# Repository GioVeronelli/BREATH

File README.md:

<h1 align="center"> B(R)EAT(H) </h1>

## Getting Started
### Clone the repository
Run the command on your terminal at the desired location:
```
git clone git@github.com:ltebs-polimi/AY2324_II_Project-1.git
```
### Dependencies
It is recommended to create a virtual environment to run the GUI. This can be done by running on your terminal:
```
python -m virtualenv GUI_venv
```
The latest versions of these libraries should then be installed within the virtual environment:
- ```PyQt5```
- ```numpy```
- ```scipy```
- ```pandas```
- ```openpyxl```
- ```pyqtgraph```
- ```os```
- ```sys```
- ```time```
- ```logging```
- ```struct```
- ```subprocess```
- ```sqlite3```
- ```csv```
- ```datetime```
- ```serial```
## Filetree
Directories are organized as follows:
```
││├───CASE
│││   └──STL files
│││
││├───GUI
│││   ├──pyqt5_venv
│││   └──GUI.py
│││
││├───PCB
│││   ├──B(R)EAT(H).bdr
│││   └──B(R)EAT(H).sch
│││
││└───PSoC_code
││    ├──GatheringData.cydsn
││       │
││       ├───Generated_Source
││       │   └───PSoC5
││       └───TopDesign
││
│└───Validation_Study
│    ├──Output_Measurements
│    └──Plots
│
└───Images

```

## Intro
There are several methods for assessing general respiratory health. The most common methods are pulmonary function tests (PFTs) that range from simple spirometry, which can be used to assess a patient’s airflow, to full body plethysmography used to assess lung volumes. Other methods include arterial blood sampling and diffusion capacity. While these evaluations are effective in assessing a patient’s respiratory health at a specific point in time in a laboratory setting, they cannot continuously monitor a patient’s respiratory state under normal daily environments. Moreover, PFTs such as spirometry require the patient to breathe maximally into a mouthpiece, a maneuver that is challenging, which makes these types of tests difficult to ensure accurate readings and are not suitable for long term use.[^1] Other methods for sensing the respiratory signal include measuring airflow through the nostrils with a pressure transducer in combination with a spirometer, and tracking chest wall movement with a piezoelectric belt.[^2] These techniques are essential for monitoring breathing of patients with respiartory disorders,chronic obstructive pulmonary disease, or neuromuscolar disorders, as they allow for the assessment of the stability of their conditions. 
An emergin area of interest is the use of motion sensors, such as accelerometers fixed on the chest or abdomen, as a comfortable, and cheap method for respiratory monitoring. The main aim of the study group is to evaluate the feasibility of implementing an accelerometry-based portable device as a simple and cost-effective solution for monitoring breathing patterns and parameters.
Respiratory disorders significantly impair lung capacity and respiratory function thus the need of developing an accurate monitoring to prevent sever conmplication and to adjust therapies promptly. Traditional monitoring techniques, although effective, can be cumbersome and uncomfrtable for partients, restricting their mobility. Therefore, developing portable devices based on accelerometers could revolutionize the clincial management of these patients by providing precise data onc hest and abdominal movements associated with breathing, enabling continuous and non-invasive monitoring. This approach could enhance the quality of life for patients by allowing them to perform daily axctivities with fewer restrictions while ensuring accurate monitoring of their clinical condition.

However,beside the developed technical features, the ethics behind measuring the subject's respiratory parameters should also be considered. The primary goal of clinical research is to develop generalizable knowledge that improves human health or increases understanding of human biology. People who participate in clinical research make it possible to secure that knowledge ensuring at the same time that subjects involved do not suffer violations of their rights, as clinical trials can expose them to significant risks. The purpose of ethical guidelines is both to protect patient volunteers and to preserve the integrity of science.[^3]

The details of the project are discussed in the following sections:
- [Hardware](#hardware)
- [Firmware](#firmware)
- [Processing](#processing)
- [Graphical user interface](#graphical-user-interface)
- [Acquisition Protocol](#acquisition-protocol)  
- [Limitations and future developments](#limitations-and-future-developments)

   <br> 

## Hardware
### Reference Folder: `PCB`, `Case_3Dprint`
  
B(R)EAT(H) is a wereable device mainly composed by LIS3DH accelerometer hold to a 3D printed support case and then fixed position on the abdomen of the subject via an elastic band.  

<br> 

<div align="center">

</div>

<br>

The electronic circuit has been simulated in breaboard before designing the PCB.   
The electronical components used for the main module are: 
- Psoc 5LP, accelerometer LIS3DH, bluetooth module HC-O5, 9V alkaline battery, switch, linear voltage regulator LM7805, resistors (330Ω 3x), capacitors (0.1 μF 1x, 0.33μF 1x)
<br>

### 3D Printed Case design discussion:
- The 3D printed case is meant to contain the PCB with all the peripherals except for the accelerometer, which is instead fixed through screws and worn on the front of the subject depending on the user selected protocol and fixed in position by an elastic band. They were both built using Tinkercad app.

Below you can see the case for holding the accelerometer:

<br> 

<div align="center">

</div>

<br>

While here it is represented the 3d printed case design:

<br> 

<div align="center">

</div>

<br>

### Hardware functioning discussion:
- The accelerometer LIS3DH communicates with the microcontroller via I2C master-slave communication, whereas the bluetooth module communicates via UART communication.
- The accelerometer has also a connection between its interrupt pin and 2.2 pin of the microcontroller, so that it can trigger an interrupt when data are available. 
- The PSOC 5LP and all the peripherals run on 5V, so the 9V of the battery is reduced and stabilized to 5V by the linear voltage regulator LM7805 and capacitors. 
- Resistors are used to limit the current running in the RGB led and to reduce the TX signal sent by the microcontroller to the bluetooth module from 5V to 3.3V, to cope with the HC-05 input pin limitations. 
- The active buzzer is used to advice the operator that the patient is breathing in a non phisiological way.
- The RBG LED is meant to signal the connection status of the device. Initially, while the device is not yet paired with the laptop, the LED will blink in RED driven by a PWM signal with a period of 1 second and duty cycle of 50%. Successful pairing is then flagged via a fixed blue light, while during data streaming a fixed green light is shown.

From a hardware perspective, we have considered three distinct methods for interaction between the subject and the device. 
First, the subject can control the device's power using an external switch to turn it on or off. 
Second, an RGB LED provides communication with the caregiver by indicating the device’s functional status. 
Finally, the buzzer serves as an additional alert mechanism, sounding an alarm if physiological measurements exceed predefined thresholds. This setup ensures that caregivers receive immediate notifications not only through the app screen but also via a distinct auditory signal.

Here it is possible to appreciate the whole device mounted on the designed PCB obtained through the press and peel technique:

<br> 

<div align="center">

</div>

<br>

## Firmware
### Reference Folder: `PSoC_CODE`
In this section it is reported the description of the code written using PSoC Creator, regarding the firmware functionalities of the PSoC5LP for commanding B(R)EAT(H) device. In the "main.c" file we have the main recommended settings for RR measurement such as: 
- 12bit resolution with high power configuration. 
- +2/-2g full scale.
- 200Hz as ODR (Output Data Rate).

Regarding "InterruptRoutines.c", the ISR function "CY_ISR(Custom_ISR_Data)" is called whenever a new value of acceleration on the Z-axis is available. This triggers the call of the script where the data is reconstructed into its binary representation and sent to the UART TX, corresponding to the RX of the HC05 for Bluetooth communication. The data stream is triggered whenever the caregiver starts the connection with the device from the GUI, which corresponds on writing a letter "s" to the TX of the HC05, associated with the RX of the UART of the PSoC through the ISR function "CY_ISR(Custom_ISR_RX)". Indeed, this function manages signals written to the TX pin of the HC05 for setting the BUZZER,LED_R,LED_B,LED_G and PWM components depending on the device operating status. This ensures that the app user can communicate with the device both from the PSoC to the GUI through the HC05, and then back from the GUI to the PSoC. This allows to have a better interaction and dinamism in the use of the app.
The ISR function "CY_ISR(Custom_ISR_RX)" is commands the RGB led and BUZZER based on the character received from the GUI which is linked to the functioning status of the device. When turned on, the PWM on LED_R blinks with a frequency of 1 second and a duty cycle of 50%. Successful pairing is then flagged via a fixed blue light, while a fixed green light is shown during data streaming. If the RR parameter is out of physiological range, depending on the selected acquistion protocol, the active BUZZER is activated to alert the caregivers drawing attention to the subject's breathing and activity that triggered the BUZZER. 

## Processing
### Reference Folder: `GUI`

For the device, two distinct data processing procedures were developed: one for real-time data processing and the other for offline data processing.

#### Real-Time Data Processing

Multiple processing techniques were developed and tested. The chosen method, despite its apparent simplicity, proved to be the most effective considering both the quality of filtering and the adaptation time. The final steps for real-time processing are as follows:
- The acquired data from the serial worker is added to a buffer ('data_buffer') that stores all the measured acceleration values coming from the accelerometer.
- A moving average filter is applied to the buffered data to smooth rapid fluctuations and stabilize the signal. The chosen window size is 200 points, corresponding to 1 second of acquisition. If the buffer contains fewer than 200 data points, the filter will wait until the chosen window size is reached to start.
- Then, a third order low-pass Butterworth filter is applied to the moving average filtered data, with a chosen cutoff frequency of 0.6 Hz. The buffer size must contain at least 12 data points before applying the filter; otherwise, the filter waits until this limit is reached.
- After this processing, the peaks and lows are identified in the signal using the find_peaks algorithm from the SciPy library. This step identifies both the points of maximum, which indicate the end of an inspiration and the beginning of an expiration, and the points of minimum, which indicate the opposite in the acceleration signal. To distinguish between real and local minima and maxima, a prominence level is chosen. Specifically, when the subject is standing, the chosen prominence is 0.15, while when sitting, it is 0.05.
- To better compute the parameters and allow the filters time to adapt, the first fiducial point identified is always a minimum. If a maximum is identified before the first minimum, it is discarded. This ensures that the filtered signal always begins with the start of a respiratory cycle.
- After these computations, the parameters are computed. The chosen parameters are: the instantenous respiratory rate, the inspiratory time, the expiratory time and the inspiratory/expiratory ratio. Each of these parameters is updated every new cycle detected.
- Starting from the instantaneous RR, it is calculated as the difference between the time index of two subsequent minima. At least two lows are required to calculate this time difference.
- The inspiratory time is calculated as the time elapsed between a peak and the previous detected minimum. At least one minimum and the subsequent peak are required for this computation.
- The expiratory time is calculated as the time elapsed between a peak and the next detected minimum. At least one peak and the subsequent minimum are required for this computation.
- Finally, the Inspiratory/Expiratory (I/E) ratio is computed as the ratio between the inspiratory time and expiratory time of each detected cycle.

The real-time data processing is summarized in the flowchart below:

<br> 

<div align="center">

</div>

<br>

#### Offline Data Processing

An offline data processing feature was added to allow users to view previous recordings. The steps followed for offline processing are as follows:
- The data are loaded from a CSV file into a DataFrame.
- The first filtering step is performed by removing the DC offset from the data by subtracting the mean of the signal from each data point
- Then, a third-order bandpass Butterworth filter is applied, with chosen cutoff frequencies 0.1 Hz and 0.6 Hz
- The peaks and lows of the filtered signal are detected once again using the 'find_peaks' algorithm from the SciPy library. A prominence criterion of 0.01 is applied to distinguish between real peaks and lows from local fluctuations.
- Multiple adjacent peaks and adjacent lows are often found. To address this issue, adjacent peaks and lows are grouped, and the midpoint is computed to obtain accurate fiducial points.
- The parameters are then extracted. Specifically, the mean respiratory rate, mean inspiratory time, mean expiratory time, and inspiratory/expiratory ratio are computed.

The offline data processing is summarized in the flowchart below:

<br> 

<div align="center">

</div>

<br>

## Graphical user interface
### Reference Folder: `GUI`

The application was developed with the primary objective of tailoring the user experience for each individual using the device. It was designed to be accessible and intuitive, ensuring efficiency and ease of use. This chapter provides a detailed, step-by-step explanation of all the landing pages and functionalities designed within the application.

#### Login Page: `LOGIN.py`

The first page features a secure login interface. Users who are already registered on the device, can enter their credentials to proceed. Otherwise, they have the option to register themselves on the registration page. The system enforces a simply password policy requiring it to be greater than 10 characters, otherwise a notification is displayed on the screen for advicing the user of this requirement.
The main functioning of both the LOGIN.py and USER.py scripts relies on the SQLite database which is needed to be installed in the device currently running B(R)EAT(H) app. For sake of clarity, the database in our project is called "user.db".

<br> 

<div align="center">

</div>

<br>

#### Registration Page: `USER.py`

On the registration page, new users can create an account. The fields included in the registration are First Name, Last Name, Phone Number, Email Address, Username, and Password, but only the latter two are mandatory at this moment for privacy reasons. Once the new user submits their information, their details are registered in a local database ('user.db'). This database is then referenced when the user logs in. After registration, the user can return to the login page and log in with their newly created credentials.

<br> 

<div align="center">

</div>

<br>

#### Acquistion Mode Choice: `Protocol.py`

As the users log in, they are presented with a selection interface for choosing the acquisition mode. Specifically, they can select from four different positions for the acquisition:
- Option 1: The subject is standing, and the accelerometer is placed on the subject's chest.
- Option 2: The subject is standing, and the accelerometer is placed on the subject's abdomen.
- Option 3: The subject is sitting, and the accelerometer is placed on the subject's abdomen.
- Option 4: The subject is sitting, and the accelerometer is placed on the subject's chest.

These different placements for the accelerometer accommodate the fact that different subjects may exhibit either chest or abdominal respiration, allowing for a more accurate and individualized data collection.

As seen from the GIF below, the page is personalized with the name of the logged-in user. Once one of the options is selected, it is highlighted, and the "Enter" button becomes available.

<br> 

<div align="center">

</div>

<br>

#### Dashboard: `PythonGUI.py`

Upon acquisition mode selection, users are directed to the main data acquisition screen. This interface is designed for real-time data visualization, enabling users to monitor respiratory patterns and view computed parameters.
The primary area of the screen is dedicated to a chart that displays real-time data from the device. Several controls are included to operate on the app. The following image displays all of them, and then we will farther investigate the functionalities.

<br> 

<div align="center">

</div>

<br>

At the bottom of the screen:
- Combobox for Connecting Device Selection: allows users to select the device to connect to. (1)
- Scan: scans for available Bluetooth (BT) devices for connection. This button is connected to the 'serialscan' function. (2)
- Connect/Disconnect: toggles between connecting and disconnecting to the chosen device. This button is connected to both the 'serial_connect' and 'serial_disconnect' functions.(3)
- Start Acquisition/Stop Acquisition: toggles between starting and stopping the data acquisition. This button is connected to both the 'start_acquisition' and 'stop_acquisition' functions. It is made available only when the app is successfully connected to the device. This triggers the sending of the letter "s" to the HC-05 for the triggering of the sending of the stream of data. If Stop Acquisition is pressed, the letter "v" is sent to the PSoC for stopping the streaming. (4)
- Save: allows users to locally save the raw data acquired during the session. When pressed, the user's local directory opens, and they can choose where to save the data as a CSV file. The file is saved with the name format "Username"+"Acquisition Mode"+"Start Time"+"End Time". It is made available only when the acquisition stream is stopped. (5)
- Show Summary: displays a table with all the instantaneous parameters computed during the acquisition. It is made available only when the acquisition stream is stopped. (6)

On the top right of the screen two buttons are available:
- Reset: allows the user to reset all the data, including both raw data and filtered data, as well as the computed parameters. This button can be pressed either during an acquisition or afterward before starting a new session. (7)
- Switch to Filtered Data/Switch to Raw Data: toggles between displaying the raw data chart and the filtered data chart, providing users with the option to view either the raw data or the processed, filtered data. (8)
Moreover, it is possible to see the name of the user displayed.

On the top left of the screen there are two tabs:
- File: from this tab the user can:
   - Start acquisition
   - Stop acquisition
   - Save data
   - Load data: Allows users to upload raw data acquired during a previous session. Initially, only the raw data are displayed. However, after pressing the 'Switch to Filtered Data' button, filtering and peak detection are performed, and the mean Respiratory Rate (RR), mean Inspiratory Time, mean Expiratory Time, and I/E Ratio are displayed in the parameters boxes. (9)
- ?: displays instructions regarding the usage of the application. (10)

Finally, on the right side of the screen, we have two main elements:
- Parameters Boxes: These boxes display the values of various parameters, computed as explained in the processing chapter. These parameters include mean Respiratory Rate (RR), mean Inspiratory Time, mean Expiratory Time, and the I/E Ratio. Whenever physiological treshold are overcome, a letter "o" is sent to the PSoC for triggering the BUZZER alarm and Switching on the LED_G. (11)
- Acquiring Method Switch Button: This button not only indicates the current acquisition method but also allows users to change the acquisition mode without repeating the login procedure. When pressed, it opens the acquisition mode selection interface. (12)

## Validation: `Validation.ipynb`

The validation of the device could not be performed using a gold standard device due to its unavailability. Consequently, we conducted the validation using three distinct protocols to assess the repeatability and sensitivity of the device. Each protocol was repeated three times for each subject across all four available acquisition modalities to ensure sufficient data for statistical analysis. The protocols were as follows:

- Protocol 1: The subject was asked to maintain a respiratory cycle of 12 breaths per minute (5-second cycles) for 1 minute.
- Protocol 2: The subject was asked to maintain a respiratory cycle of 15 breaths per minute (4-second cycles) for 1 minute.
- Protocol 3: The subject was asked to maintain a respiratory cycle of 12 breaths per minute (5-second cycles) for 30 seconds, followed by a respiratory cycle of 15 breaths per minute (4-second cycles) for the next 30 seconds.
Additionally, we performed Protocol 4, where the subject breathed freely while being recorded to observe the correspondence between the observed movement and the acquired data.

After acquiring the data, all computed parameters were saved. The RRs were plotted in a graph, with the goal respiratory cycle displayed, allowing for qualitative analysis of the device's performance. For quantitative analysis, basic statistics were computed: mean squared error (MSE), mean absolute error (MAE), root mean square error (RMSE), and the standard deviation. These statistics were calculated for each protocol and each acquisition option separately, as well as providing an overall insight into the performance across all protocols.

Due to time constraints in completing the prototype, the full validation process was conducted on only one subject. However, to assess inter-subject variability to some extent, Protocols 1 and 3 were performed on a second subject, with one acquisition per option. Although this sample size is not statistically significant, it provides preliminary insights for the project and is deemed acceptable for the current stage.
Moreover, the validation focused on proving the efficacy of the Respiratory Rate (RR) computation. Indeed, following a strict protocol for monitored inspiration and expiration proved to be very challenging. The use of a gold standard device is crucial for the accurate validation of these parameters.

### Results for the First Subject
### Protocol 1 Results

The results obtained for Protocol 1 are hereby reported:

##### Option 1
<br> 
<table>
    <tr>
        <td>
            
        </td>
        <td>
            <table border="1">
                <tr>
                    <th>Measure</th>
                    <th>Value (breaths/min)</th>
                </tr>
                <tr>
                    <td>MSE</td>
                    <td>1.27</td>
                </tr>
                <tr>
                    <td>MAE</td>
                    <td>0.8</td>
                </tr>
                <tr>
                    <td>RMSE</td>
                    <td>1.13</td>
                </tr>
                <tr>
                    <td>Standard Deviation</td>
                    <td>1.07</td>
                </tr>
            </table>
        </td>
    </tr>
</table>
<br>

##### Option 2
<br> 
<table>
    <tr>
        <td>
            
        </td>
        <td>
            <table border="1">
                <tr>
                    <th>Measure</th>
                    <th>Value (breaths/min)</th>
                </tr>
                <tr>
                    <td>MSE</td>
                    <td>0.74</td>
                </tr>
                <tr>
                    <td>MAE</td>
                    <td>0.68</td>
                </tr>
                <tr>
                    <td>RMSE</td>
                    <td>0.86</td>
                </tr>
                <tr>
                    <td>Standard Deviation</td>
                    <td>0.83</td>
                </tr>
            </table>
        </td>
    </tr>
</table>
<br>

##### Option 3
<br>
<table>
    <tr>
        <td>
            
        </td>
        <td>
            <table border="1">
                <tr>
                    <th>Measure</th>
                    <th>Value (breaths/min)</th>
                </tr>
                <tr>
                    <td>MSE</td>
                    <td>0.45</td>
                </tr>
                <tr>
                    <td>MAE</td>
                    <td>0.45</td>
                </tr>
                <tr>
                    <td>RMSE</td>
                    <td>0.67</td>
                </tr>
                <tr>
                    <td>Standard Deviation</td>
                    <td>0.62</td>
                </tr>
            </table>
        </td>
    </tr>
</table>
<br>

##### Option 4
<br> 
<table>
    <tr>
        <td>
            
        </td>
        <td>
            <table border="1">
                <tr>
                    <th>Measure</th>
                    <th>Value (breaths/min)</th>
                </tr>
                <tr>
                    <td>MSE</td>
                    <td>1.69</td>
                </tr>
                <tr>
                    <td>MAE</td>
                    <td>0.94</td>
                </tr>
                <tr>
                    <td>RMSE</td>
                    <td>1.30</td>
                </tr>
                <tr>
                    <td>Standard Deviation</td>
                    <td>1.30</td>
                </tr>
            </table>
        </td>
    </tr>
</table>
<br>

##### Overall
<br> 
<table>
    <tr>
        <td>
            
        </td>
        <td>
            <table border="1">
                <tr>
                    <th>Measure</th>
                    <th>Value (breaths/min)</th>
                </tr>
                <tr>
                    <td>MSE</td>
                    <td>1.05</td>
                </tr>
                <tr>
                    <td>MAE</td>
                    <td>0.72</td>
                </tr>
                <tr>
                    <td>RMSE</td>
                    <td>1.02</td>
                </tr>
                <tr>
                    <td>Standard Deviation</td>
                    <td>1.01</td>
                </tr>
            </table>
        </td>
    </tr>
</table>
<br>

#### Protocol 1 Discussion

The results from Protocol 1 demonstrate that the device performs best when the accelerometer is placed on the abdomen while the subject is sitting, as indicated by the lowest MSE, MAE, RMSE, and standard deviation. This suggests that the abdomen placement is more stable and less affected by external movements compared to the chest placement. However, it is important to highlight that, despite the abdomen placement showing superior stability, the chest placement also performed well and remains a viable option.

### Protocol 2 Results

The results obtained for Protocol 2 are hereby reported:

##### Option 1
<br> 
<table>
    <tr>
        <td>
            
        </td>
        <td>
            <table border="1">
                <tr>
                    <th>Measure</th>
                    <th>Value (breaths/min)</th>
                </tr>
                <tr>
                    <td>MSE</td>
                    <td>4.92</td>
                </tr>
                <tr>
                    <td>MAE</td>
                    <td>1.24</td>
                </tr>
                <tr>
                    <td>RMSE</td>
                    <td>2.22</td>
                </tr>
                <tr>
                    <td>Standard Deviation</td>
                    <td>2.06</td>
                </tr>
            </table>
        </td>
    </tr>
</table>
<br>

##### Option 2
<br> 
<table>
    <tr>
        <td>
            
        </td>
        <td>
            <table border="1">
                <tr>
                    <th>Measure</th>
                    <th>Value (breaths/min)</th>
                </tr>
                <tr>
                    <td>MSE</td>
                    <td>1.0</td>
                </tr>
                <tr>
                    <td>MAE</td>
                    <td>0.67</td>
                </tr>
                <tr>
                    <td>RMSE</td>
                    <td>1.0</td>
                </tr>
                <tr>
                    <td>Standard Deviation</td>
                    <td>0.82</td>
                </tr>
            </table>
        </td>
    </tr>
</table>
<br>

##### Option 3
<br>
<table>
    <tr>
        <td>
            
        </td>
        <td>
            <table border="1">
                <tr>
                    <th>Measure</th>
                    <th>Value (breaths/min)</th>
                </tr>
                <tr>
                    <td>MSE</td>
                    <td>0.74</td>
                </tr>
                <tr>
                    <td>MAE</td>
                    <td>0.59</td>
                </tr>
                <tr>
                    <td>RMSE</td>
                    <td>0.86</td>
                </tr>
                <tr>
                    <td>Standard Deviation</td>
                    <td>0.71</td>
                </tr>
            </table>
        </td>
    </tr>
</table>
<br>

##### Option 4
<br> 
<table>
    <tr>
        <td>
            
        </td>
        <td>
            <table border="1">
                <tr>
                    <th>Measure</th>
                    <th>Value (breaths/min)</th>
                </tr>
                <tr>
                    <td>MSE</td>
                    <td>1.58</td>
                </tr>
                <tr>
                    <td>MAE</td>
                    <td>0.78</td>
                </tr>
                <tr>
                    <td>RMSE</td>
                    <td>1.25</td>
                </tr>
                <tr>
                    <td>Standard Deviation</td>
                    <td>1.24</td>
                </tr>
            </table>
        </td>
    </tr>
</table>
<br>

##### Overall
<br> 
<table>
    <tr>
        <td>
            
        </td>
        <td>
            <table border="1">
                <tr>
                    <th>Measure</th>
                    <th>Value (breaths/min)</th>
                </tr>
                <tr>
                    <td>MSE</td>
                    <td>2.0</td>
                </tr>
                <tr>
                    <td>MAE</td>
                    <td>0.81</td>
                </tr>
                <tr>
                    <td>RMSE</td>
                    <td>1.41</td>
                </tr>
                <tr>
                    <td>Standard Deviation</td>
                    <td>1.32</td>
                </tr>
            </table>
        </td>
    </tr>
</table>
<br>

### Protocol 2 Discussion

Similar to Protocol 1, the results from Protocol 2 indicate that the device provides more accurate measurements when the accelerometer is placed on the abdomen, particularly when the subject is sitting. The highest errors are observed when the accelerometer is placed on the chest while standing, suggesting higher variability and potential interference from body movements, as it is possible to see from the two outliers seen in Option 1 chart.

### Protocol 3 Results

The results obtained for Protocol 3 are hereby reported:

##### Option 1
<br> 
<table>
    <tr>
        <td>
            
        </td>
        <td>
            <table border="1">
                <tr>
                    <th>Measure</th>
                    <th>Value (breaths/min)</th>
                </tr>
                <tr>
                    <td>MSE</td>
                    <td>0.87</td>
                </tr>
                <tr>
                    <td>MAE</td>
                    <td>0.73</td>
                </tr>
                <tr>
                    <td>RMSE</td>
                    <td>0.93</td>
                </tr>
                <tr>
                    <td>Standard Deviation</td>
                    <td>0.91</td>
                </tr>
            </table>
            <table border="1">
                <tr>
                    <th>Measure</th>
                    <th>Value (breaths/min)</th>
                </tr>
                <tr>
                    <td>MSE</td>
                    <td>3.68</td>
                </tr>
                <tr>
                    <td>MAE</td>
                    <td>1.5</td>
                </tr>
                <tr>
                    <td>RMSE</td>
                    <td>1.92</td>
                </tr>
                <tr>
                    <td>Standard Deviation</td>
                    <td>1.76</td>
                </tr>
            </table>
        </td>
    </tr>
</table>
<br>

##### Option 2
<br> 
<table>
    <tr>
        <td>
            
        </td>
        <td>
            <table border="1">
                <tr>
                    <th>Measure</th>
                    <th>Value (breaths/min)</th>
                </tr>
                <tr>
                    <td>MSE</td>
                    <td>0.53</td>
                </tr>
                <tr>
                    <td>MAE</td>
                    <td>0.4</td>
                </tr>
                <tr>
                    <td>RMSE</td>
                    <td>0.73</td>
                </tr>
                <tr>
                    <td>Standard Deviation</td>
                    <td>0.72</td>
                </tr>
            </table>
            <table border="1">
                <tr>
                    <th>Measure</th>
                    <th>Value (breaths/min)</th>
                </tr>
                <tr>
                    <td>MSE</td>
                    <td>2.62</td>
                </tr>
                <tr>
                    <td>MAE</td>
                    <td>1.29</td>
                </tr>
                <tr>
                    <td>RMSE</td>
                    <td>1.62</td>
                </tr>
                <tr>
                    <td>Standard Deviation</td>
                    <td>1.58</td>
                </tr>
            </table>
        </td>
    </tr>
</table>
<br>

##### Option 3
<br> 
<table>
    <tr>
        <td>
            
        </td>
        <td>
            <table border="1">
                <tr>
                    <th>Measure</th>
                    <th>Value (breaths/min)</th>
                </tr>
                <tr>
                    <td>MSE</td>
                    <td>1.0</td>
                </tr>
                <tr>
                    <td>MAE</td>
                    <td>0.73</td>
                </tr>
                <tr>
                    <td>RMSE</td>
                    <td>1.0</td>
                </tr>
                <tr>
                    <td>Standard Deviation</td>
                    <td>0.68</td>
                </tr>
            </table>
            <table border="1">
                <tr>
                    <th>Measure</th>
                    <th>Value (breaths/min)</th>
                </tr>
                <tr>
                    <td>MSE</td>
                    <td>1.33</td>
                </tr>
                <tr>
                    <td>MAE</td>
                    <td>0.95</td>
                </tr>
                <tr>
                    <td>RMSE</td>
                    <td>1.15</td>
                </tr>
                <tr>
                    <td>Standard Deviation</td>
                    <td>1.65</td>
                </tr>
            </table>
        </td>
    </tr>
</table>
<br>

##### Option 4
<br> 
<table>
    <tr>
        <td>
            
        </td>
        <td>
            <table border="1">
                <tr>
                    <th>Measure</th>
                    <th>Value (breaths/min)</th>
                </tr>
                <tr>
                    <td>MSE</td>
                    <td>0.93</td>
                </tr>
                <tr>
                    <td>MAE</td>
                    <td>0.8</td>
                </tr>
                <tr>
                    <td>RMSE</td>
                    <td>0.97</td>
                </tr>
                <tr>
                    <td>Standard Deviation</td>
                    <td>0.96</td>
                </tr>
            </table>
            <table border="1">
                <tr>
                    <th>Measure</th>
                    <th>Value (breaths/min)</th>
                </tr>
                <tr>
                    <td>MSE</td>
                    <td>0.85</td>
                </tr>
                <tr>
                    <td>MAE</td>
                    <td>0.65</td>
                </tr>
                <tr>
                    <td>RMSE</td>
                    <td>0.92</td>
                </tr>
                <tr>
                    <td>Standard Deviation</td>
                    <td>0.74</td>
                </tr>
            </table>
        </td>
    </tr>
</table>
<br>

##### Overall
<br> 
<table>
    <tr>
        <td>
            
        </td>
        <td>
            <table border="1">
                <tr>
                    <th>Measure</th>
                    <th>Value (breaths/min)</th>
                </tr>
                <tr>
                    <td>MSE</td>
                    <td>0.83</td>
                </tr>
                <tr>
                    <td>MAE</td>
                    <td>0.67</td>
                </tr>
                <tr>
                    <td>RMSE</td>
                    <td>0.91</td>
                </tr>
                <tr>
                    <td>Standard Deviation</td>
                    <td>0.88</td>
                </tr>
            </table>
            <table border="1">
                <tr>
                    <th>Measure</th>
                    <th>Value (breaths/min)</th>
                </tr>
                <tr>
                    <td>MSE</td>
                    <td>2.15</td>
                </tr>
                <tr>
                    <td>MAE</td>
                    <td>1.11</td>
                </tr>
                <tr>
                    <td>RMSE</td>
                    <td>1.48</td>
                </tr>
                <tr>
                    <td>Standard Deviation</td>
                    <td>1.31</td>
                </tr>
            </table>
        </td>
    </tr>
</table>
<br>

### Protocol 3 Discussion

Protocol 3's results reaffirm the trend observed in the previous protocols, with the abdomen placement providing the best results. The mixed breathing rates add complexity to the data, but the device handles these variations really well, with better performance noted during sitting positions.

### Discussion

The statistical analysis across the three protocols demonstrates that the B(R)EAT(H) device provides reliable respiratory rate (RR) measurements, particularly when the accelerometer is placed on the abdomen. This placement minimizes interference from chest movements, resulting in lower error rates and greater stability in the readings. It is important to note that the subject who performed the analysis prefers abdominal respiration, which may have contributed to these findings. Further inter-subject analyses are needed to validate this observation across a broader population.
Furthermore, the device exhibited high performance in both repeatability and sensitivity tests, maintaining good accuracy during stable breathing rates and correctly identifying sudden changes in respiratory rate. This highlights the device's robustness and effectiveness in various respiratory conditions.

### Results for the Second Subject
### Protocol 1 Results

The results obtained for Protocol 1 are hereby reported:

##### Option 1
<br> 
<table>
    <tr>
        <td>
            
        </td>
        <td>
            <table border="1">
                <tr>
                    <th>Measure</th>
                    <th>Value (breaths/min)</th>
                </tr>
                <tr>
                    <td>MSE</td>
                    <td>0.9</td>
                </tr>
                <tr>
                    <td>MAE</td>
                    <td>0.7</td>
                </tr>
                <tr>
                    <td>RMSE</td>
                    <td>0.95</td>
                </tr>
                <tr>
                    <td>Standard Deviation</td>
                    <td>0.94</td>
                </tr>
            </table>
        </td>
    </tr>
</table>
<br>

##### Option 2
<br> 
<table>
    <tr>
        <td>
            
        </td>
        <td>
            <table border="1">
                <tr>
                    <th>Measure</th>
                    <th>Value (breaths/min)</th>
                </tr>
                <tr>
                    <td>MSE</td>
                    <td>0.8</td>
                </tr>
                <tr>
                    <td>MAE</td>
                    <td>0.6</td>
                </tr>
                <tr>
                    <td>RMSE</td>
                    <td>0.89</td>
                </tr>
                <tr>
                    <td>Standard Deviation</td>
                    <td>0.8</td>
                </tr>
            </table>
        </td>
    </tr>
</table>
<br>

##### Option 3
<br>
<table>
    <tr>
        <td>
            
        </td>
        <td>
            <table border="1">
                <tr>
                    <th>Measure</th>
                    <th>Value (breaths/min)</th>
                </tr>
                <tr>
                    <td>MSE</td>
                    <td>0.83</td>
                </tr>
                <tr>
                    <td>MAE</td>
                    <td>0.5</td>
                </tr>
                <tr>
                    <td>RMSE</td>
                    <td>0.91</td>
                </tr>
                <tr>
                    <td>Standard Deviation</td>
                    <td>0.91</td>
                </tr>
            </table>
        </td>
    </tr>
</table>
<br>

##### Option 4
<br> 
<table>
    <tr>
        <td>
            
        </td>
        <td>
            <table border="1">
                <tr>
                    <th>Measure</th>
                    <th>Value (breaths/min)</th>
                </tr>
                <tr>
                    <td>MSE</td>
                    <td>1.09</td>
                </tr>
                <tr>
                    <td>MAE</td>
                    <td>0.91</td>
                </tr>
                <tr>
                    <td>RMSE</td>
                    <td>1.04</td>
                </tr>
                <tr>
                    <td>Standard Deviation</td>
                    <td>1.03</td>
                </tr>
            </table>
        </td>
    </tr>
</table>
<br>

##### Overall
<br> 
<table>
    <tr>
        <td>
            
        </td>
        <td>
            <table border="1">
                <tr>
                    <th>Measure</th>
                    <th>Value (breaths/min)</th>
                </tr>
                <tr>
                    <td>MSE</td>
                    <td>0.91</td>
                </tr>
                <tr>
                    <td>MAE</td>
                    <td>0.67</td>
                </tr>
                <tr>
                    <td>RMSE</td>
                    <td>0.95</td>
                </tr>
                <tr>
                    <td>Standard Deviation</td>
                    <td>0.95</td>
                </tr>
            </table>
        </td>
    </tr>
</table>
<br>

### Protocol 1 Discussion

The results indicate that the abdomen placement, particularly while sitting, provides more stable readings with lower error metrics. The chest placements show an improved performance compared to the first subject, with reduction in all error metrics, but still with slightly higher variability compared to the abdomen placement. 

### Protocol 3 Results

The results obtained for Protocol 3 are hereby reported:

##### Option 1
<br> 
<table>
    <tr>
        <td>
            
        </td>
        <td>
            <table border="1">
                <tr>
                    <th>Measure</th>
                    <th>Value (breaths/min)</th>
                </tr>
                <tr>
                    <td>MSE</td>
                    <td>0.4</td>
                </tr>
                <tr>
                    <td>MAE</td>
                    <td>0.4</td>
                </tr>
                <tr>
                    <td>RMSE</td>
                    <td>0.63</td>
                </tr>
                <tr>
                    <td>Standard Deviation</td>
                    <td>0.49</td>
                </tr>
            </table>
            <table border="1">
                <tr>
                    <th>Measure</th>
                    <th>Value (breaths/min)</th>
                </tr>
                <tr>
                    <td>MSE</td>
                    <td>1.43</td>
                </tr>
                <tr>
                    <td>MAE</td>
                    <td>0.86</td>
                </tr>
                <tr>
                    <td>RMSE</td>
                    <td>1.20</td>
                </tr>
                <tr>
                    <td>Standard Deviation</td>
                    <td>0.83</td>
                </tr>
            </table>
        </td>
    </tr>
</table>
<br>

##### Option 2
<br> 
<table>
    <tr>
        <td>
            
        </td>
        <td>
            <table border="1">
                <tr>
                    <th>Measure</th>
                    <th>Value (breaths/min)</th>
                </tr>
                <tr>
                    <td>MSE</td>
                    <td>0.6</td>
                </tr>
                <tr>
                    <td>MAE</td>
                    <td>0.6</td>
                </tr>
                <tr>
                    <td>RMSE</td>
                    <td>0.77</td>
                </tr>
                <tr>
                    <td>Standard Deviation</td>
                    <td>0.49</td>
                </tr>
            </table>
            <table border="1">
                <tr>
                    <th>Measure</th>
                    <th>Value (breaths/min)</th>
                </tr>
                <tr>
                    <td>MSE</td>
                    <td>1.0</td>
                </tr>
                <tr>
                    <td>MAE</td>
                    <td>0.71</td>
                </tr>
                <tr>
                    <td>RMSE</td>
                    <td>1.0</td>
                </tr>
                <tr>
                    <td>Standard Deviation</td>
                    <td>0.70</td>
                </tr>
            </table>
        </td>
    </tr>
</table>
<br>

##### Option 3
<br> 
<table>
    <tr>
        <td>
            
        </td>
        <td>
            <table border="1">
                <tr>
                    <th>Measure</th>
                    <th>Value (breaths/min)</th>
                </tr>
                <tr>
                    <td>MSE</td>
                    <td>0.4</td>
                </tr>
                <tr>
                    <td>MAE</td>
                    <td>0.4</td>
                </tr>
                <tr>
                    <td>RMSE</td>
                    <td>0.63</td>
                </tr>
                <tr>
                    <td>Standard Deviation</td>
                    <td>0.49</td>
                </tr>
            </table>
            <table border="1">
                <tr>
                    <th>Measure</th>
                    <th>Value (breaths/min)</th>
                </tr>
                <tr>
                    <td>MSE</td>
                    <td>1.14</td>
                </tr>
                <tr>
                    <td>MAE</td>
                    <td>0.86</td>
                </tr>
                <tr>
                    <td>RMSE</td>
                    <td>1.07</td>
                </tr>
                <tr>
                    <td>Standard Deviation</td>
                    <td>1.03</td>
                </tr>
            </table>
        </td>
    </tr>
</table>
<br>

##### Option 4
<br> 
<table>
    <tr>
        <td>
            
        </td>
        <td>
            <table border="1">
                <tr>
                    <th>Measure</th>
                    <th>Value (breaths/min)</th>
                </tr>
                <tr>
                    <td>MSE</td>
                    <td>0.6</td>
                </tr>
                <tr>
                    <td>MAE</td>
                    <td>0.6</td>
                </tr>
                <tr>
                    <td>RMSE</td>
                    <td>0.77</td>
                </tr>
                <tr>
                    <td>Standard Deviation</td>
                    <td>0.49</td>
                </tr>
            </table>
            <table border="1">
                <tr>
                    <th>Measure</th>
                    <th>Value (breaths/min)</th>
                </tr>
                <tr>
                    <td>MSE</td>
                    <td>1.14</td>
                </tr>
                <tr>
                    <td>MAE</td>
                    <td>0.86</td>
                </tr>
                <tr>
                    <td>RMSE</td>
                    <td>1.07</td>
                </tr>
                <tr>
                    <td>Standard Deviation</td>
                    <td>1.07</td>
                </tr>
            </table>
        </td>
    </tr>
</table>
<br>

##### Overall
<br> 
<table>
    <tr>
        <td>
            
        </td>
        <td>
            <table border="1">
                <tr>
                    <th>Measure</th>
                    <th>Value (breaths/min)</th>
                </tr>
                <tr>
                    <td>MSE</td>
                    <td>0.5</td>
                </tr>
                <tr>
                    <td>MAE</td>
                    <td>0.5</td>
                </tr>
                <tr>
                    <td>RMSE</td>
                    <td>0.71</td>
                </tr>
                <tr>
                    <td>Standard Deviation</td>
                    <td>0.5</td>
                </tr>
            </table>
            <table border="1">
                <tr>
                    <th>Measure</th>
                    <th>Value (breaths/min)</th>
                </tr>
                <tr>
                    <td>MSE</td>
                    <td>1.18</td>
                </tr>
                <tr>
                    <td>MAE</td>
                    <td>0.82</td>
                </tr>
                <tr>
                    <td>RMSE</td>
                    <td>1.09</td>
                </tr>
                <tr>
                    <td>Standard Deviation</td>
                    <td>0.98</td>
                </tr>
            </table>
        </td>
    </tr>
</table>
<br>

### Protocol 3 Discussion

The mixed breathing rates protocol showed once again that the device could handle variations in respiratory rate well. The abdomen placements again provided more stable and accurate readings compared to chest placements. Even in Protocol 3 the second subject's chest placement data for Protocol 3 show a significant improvement in error metrics compared to the first subject for the 12 breaths per minute segment, with large reductions in MSE and RMSE. This indicates much better stability and accuracy. However, for the 15 breaths per minute segment, while improvements are noted in some metrics, the overall performance is slightly mixed, suggesting some variability.

### Discussion

For Subject 2, the device once again proved its efficacy and reliability in measurements, both during stability and sensitivity tests. Similar to the first subject, the best results were obtained with the accelerometer placed on the abdomen. However, in this case, the performance of the chest placement improved significantly. It is important to highlight that this subject, unlike the first, prefers chest respiration. This indicates that the device is sensitive to individual respiration preferences and suggests that performance might further improve if it becomes less sensitive to chest movements.

### Inter-Subject Discussion

The inclusion of a second subject allowed for a preliminary inter-subject analysis, revealing notable trends despite the limited number of tests. Both subjects exhibited better performance when the accelerometer was placed on the abdomen, especially in the sitting position. The second subject’s results aligned with the first subject’s, showing lower error rates and greater stability with abdomen placements.

However, a key difference was observed in the chest placements. The second subject, who prefers chest respiration, showed significantly improved performance with the chest placement compared to the first subject. This suggests that the device is sensitive to individual respiration preferences and may perform better when aligned with the subject's natural breathing pattern.

This initial comparison suggests that the B(R)EAT(H) device is robust across different individuals, maintaining high accuracy and sensitivity in respiratory rate measurements. However, further studies with a larger sample size and more comprehensive testing are necessary to confirm these findings and ensure generalizability across diverse populations.

## Ethical Guidelines and Directives

### Ethical Considerations

The developement and implementation to the final users of B(R)EAT(H) must adhere to stringent ethical guidelines to ensure the safety, privacy, and well-being of participants. It is crucial to protect the users righs and maintain the integrity of the scientific investigation and of the final use of the device.
Different key points need to be addressed:
1. Informed consent: the users must be fully informed about the purpose, procedures, risks, and benefits of using the device. Information regarding the device must be delivered in a clear and understandable way.
2. Privacy and Confidentiality: personal data collected must be handled in accordance with data protection laws. In the EU, the device and its application must adhere with the General Data Protection Regulation (GDPR).
3. Risk-Benefit Analysis: the design and use of the device must aim to minimize any potential risks to users and to maximize the potential benefits in using the device.
4. Transparency and Accountability: detailed records of the studies proving the efficacy of the device must be maintained, ensuring transparency and facilitating peer review and replication of the study.
5. Approval from Ethics Committees: before starting any wide-range clinical study, approval must be obtained from external ethical committees, ensuring that the study protocols meet ethical and scientific standards.
6. Long-Term Monitoring: even after the delivery of the device to final users, a continous monitoring on the risks, benefits and efficacy of the device must be provided.

### Compliance with Directives 

The B(R)EAT(H) device must adhere to various regulatory directives, to ensure it meets safety, performance, and quality standards. Considering the EU regulatory landscape, the key directives and regulations include:
- Medical Device Regulation (MDR) 2017/745: our device falls into the scope of the MDR. In particular, following rule 10 it can be classified as a Class IIa, as it is an active device for diagnosis and monitoring not intended for a prolonged use or direct diagnosis of critical conditions. For this reason, the technical documentiation and the Quality Management System must be reviewed by a Notified Body, that will issue a CE certificate if the standards are satisfied. Post-market surveillance and vigilance activities are then crucial to ensure ongoing compliance and safety of the device.
- General Data Protection Regulation (GDPR) EU 2016/679: as already introduced in the Ethical Considerations chapter, given that the device collects personal health data, it must comply with GDPR to ensure data privacy and protection.
- Electronimagnetic Compatibility (EMC) Directive 2014/30/EU: since the device might operate in a clinical environemnt, it must comply with EMC requirements to ensure it does not emit electromagnetic interference that could affect other devices.
- Radio Equipment Directive (RED) 2014/53/EU: since a Bluetooth module is used, the device must comply with the RED.
- Waste Electrical and Electronic Equipment (WEEE/RAEE) 2012/19/EU: the device must comply with the WEEE Directive, which aims to reduce the environmental impact of electronic equipment at the end of their life cycle. 

## Limitations and future developments

Although the results achieved so far are satisfying and encouraging, there are still some challenges that need to be addressed for the device. The primary issue is the limited number of participants involved in testing. A potential solution could be to customize the processing algorithms based on individual characteristics such as height, weight, age, and sex, with the subject’s consent for using their personal data. By incorporating these variables, the device may provide more accurate and reliable RR measurements across a broader range of users.

To tackle the second challenge, we propose using two accelerometers for motion compensation. The second accelerometer can be positioned on the back, where it will be less affected by breathing but will still capture body movements. This approach aims to reduce the impact of motion on RR estimation, thereby improving the device's performance during physical activities.

The third challenge involves adding other electronic components on the device. We suggest incorporating an Analog-to-Digital Converter (ADC) to monitor the battery status and display this information in the app, allowing users to determine when a battery change is necessary. Additionally, a potentiometer can be included to adjust the buzzer sound level.

In summary, we believe these solutions will enhance the device's overall functionality and facilitate its integration into sensor-equipped garments for everyday monitoring.

## Authors

- roberto1.digiacomo@mail.polimi.it
- giovanni.veronelli@mail.polimi.it
- muhammedfurkan.beyazyuz@mail.polimi.it 
<br>

## References
[^1]: Chu, M., Nguyen, T., Pandey, V. et al. Respiration rate and volume measurements using wearable strain sensors. npj Digital Med 2, 8 (2019)
[^2]: Miller, M. R.. “Chapter 15 - Polysomnography” Handbook of clinical Neurolog, 2019 Jan. 1, 160, 381-392
[^3]: Ezekiel J. Emanuel,David Wendler,Christine Grady,What Makes Clinical Research Ethical? External Link Icon, Journal of the American Medical Association, Vol. 283, No. 20, May 24, 2000

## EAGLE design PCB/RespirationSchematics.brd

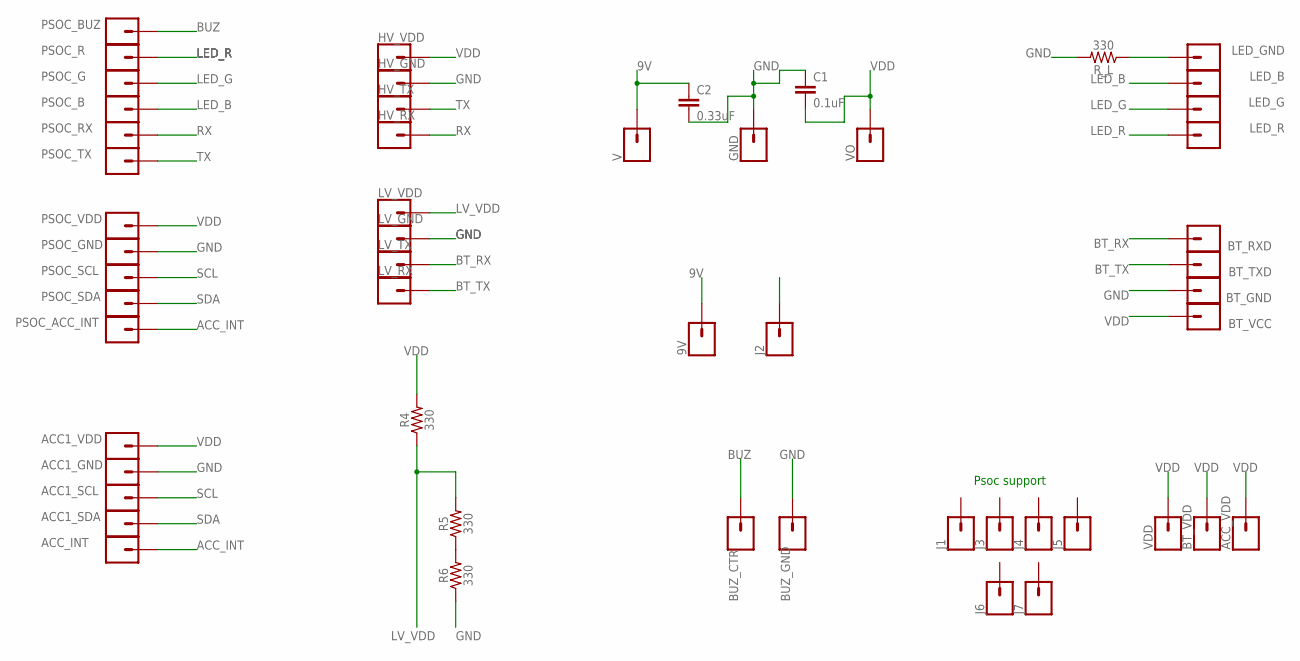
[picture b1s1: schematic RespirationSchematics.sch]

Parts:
9V: CONN_01; 1X01
ACC1_GND, ACC1_SCL, ACC1_SDA, ACC1_VDD: CONN_01; 1X01
ACC_INT: CONN_01; 1X01
ACC_VDD: CONN_01; 1X01
BT_GND: CONN_01; 1X01
BT_RXD: CONN_01; 1X01
BT_TXD: CONN_01; 1X01
BT_VCC: CONN_01; 1X01
BT_VDD: CONN_01; 1X01
BUZ_CTR: CONN_01; 1X01
BUZ_GND: CONN_01; 1X01
C1: 0.1uF; CAP-PTH-SMALL-KIT
C2: 0.33uF; CAP-PTH-SMALL-KIT
GND: CONN_01; 1X01
HV_GND: CONN_01; 1X01
HV_RX: CONN_01; 1X01
HV_TX: CONN_01; 1X01
HV_VDD: CONN_01; 1X01
J1, J2, J3, J4, J5, J6, J7: CONN_01; 1X01
LED_B: CONN_01; 1X01
LED_G: CONN_01; 1X01
LED_GND: CONN_01; 1X01
LED_R: CONN_01; 1X01
LV_GND: CONN_01; 1X01
LV_RX: CONN_01; 1X01
LV_TX: CONN_01; 1X01
LV_VDD: CONN_01; 1X01
PSOC_ACC_INT: CONN_01; 1X01
PSOC_B: CONN_01; 1X01
PSOC_BUZ: CONN_01; 1X01
PSOC_G: CONN_01; 1X01
PSOC_GND: CONN_01; 1X01
PSOC_R: CONN_01; 1X01
PSOC_RX: CONN_01; 1X01
PSOC_SCL: CONN_01; 1X01
PSOC_SDA: CONN_01; 1X01
PSOC_TX: CONN_01; 1X01
PSOC_VDD: CONN_01; 1X01
R4, R5, R6: 330; AXIAL-0.3
R_L: 330; AXIAL-0.3
V: CONN_01; 1X01
VDD: CONN_01; 1X01
VO: CONN_01; 1X01

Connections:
9V: 9V.1, C2.1, V.1
ACC_INT: ACC_INT.1, PSOC_ACC_INT.1
BT_RX: BT_RXD.1, LV_TX.1
BT_TX: BT_TXD.1, LV_RX.1
BUZ: BUZ_CTR.1, PSOC_BUZ.1
GND: ACC1_GND.1, BT_GND.1, BUZ_GND.1, C1.1, C2.2, GND.1, HV_GND.1, J2.1, LV_GND.1, PSOC_GND.1, R6.P$1 (1), R_L.P$2 (2)
LED_B: LED_B.1, PSOC_B.1
LED_G: LED_G.1, PSOC_G.1
LED_R: LED_R.1, PSOC_R.1
LV_VDD: LV_VDD.1, R4.P$1 (1), R5.P$2 (2)
unnamed: LED_GND.1, R_L.P$1 (1)
unnamed: R5.P$1 (1), R6.P$2 (2)
RX: HV_RX.1, PSOC_RX.1
SCL: ACC1_SCL.1, PSOC_SCL.1
SDA: ACC1_SDA.1, PSOC_SDA.1
TX: HV_TX.1, PSOC_TX.1
VDD: ACC1_VDD.1, ACC_VDD.1, BT_VCC.1, BT_VDD.1, C1.2, HV_VDD.1, PSOC_VDD.1, R4.P$2 (2), VDD.1, VO.1

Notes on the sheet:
Psoc support

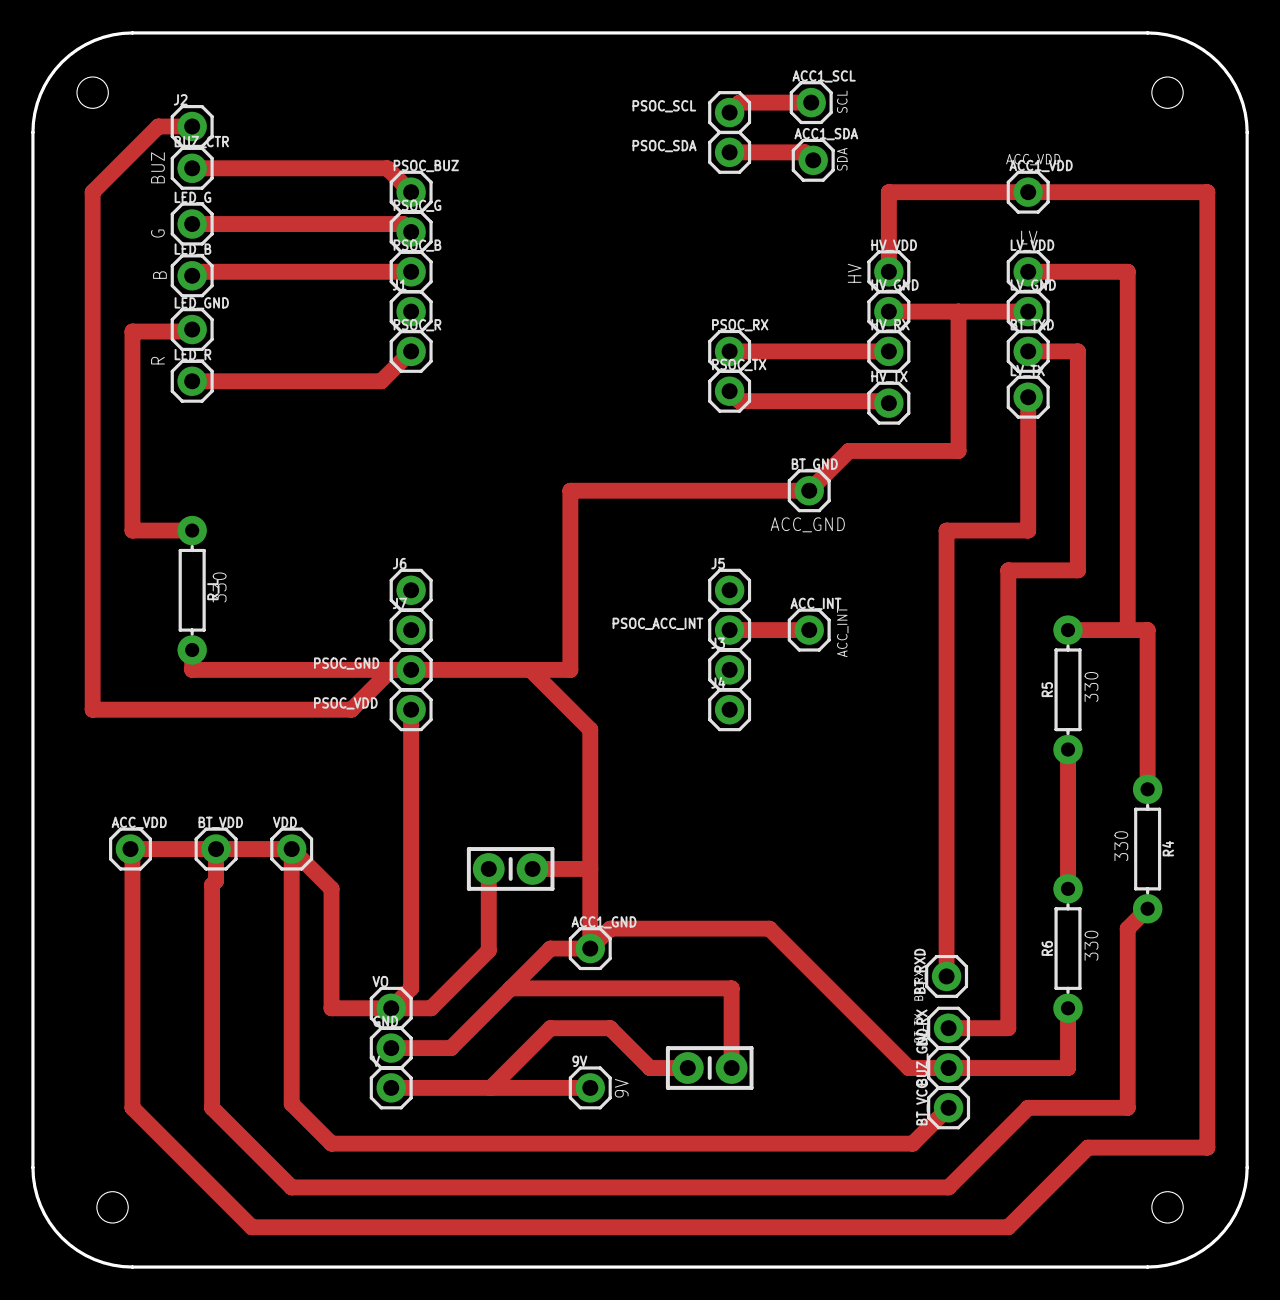
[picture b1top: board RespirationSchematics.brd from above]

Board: 2 copper layers, 77.5 x 78.7 mm, 54 parts (0 on the bottom side), 17 nets.

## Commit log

2025-03-09 Data acquired folder
2025-03-09 GUI, Images and PCB added
2025-03-09 Signal processing and User
2025-03-09 Added README
2025-03-09 PsOC Files added

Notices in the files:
parts and their libraries:
SparkFun-Connectors: Licensing: Creative Commons ShareAlike 4.0 International - https://creativecommons.org/licenses/by-sa/4.0
